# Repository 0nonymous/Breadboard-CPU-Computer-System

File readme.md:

# 8-Bit Microcoded Breadboard CPU

## Overview

This project is a fully microcoded 8-bit CPU designed from scratch and implemented using 100+ 74LS-series ICs across 40+ breadboards.

The system includes:

- Custom 8-bit CISC-style instruction set (0x00–0x45 implemented)
- 8-bit data bus
- 16-bit address bus (64KB address space)
- Fully horizontal microcoded control unit (48-bit control word)
- 6 × AT28C16 EEPROM control store
- Memory-mapped I/O
- 6522 VIA interface (32 GPIO)
- Dual-port shared memory VGA subsystem
- Custom Python two-pass assembler and ROM flashing pipeline
- Working assembly programs including Snake

This is the third architectural iteration. Earlier versions exposed architectural limitations. The current version runs reliably at approximately ~0.25 MHz.

---

## Assembly Syntax

The assembler uses suffix symbols to indicate addressing modes:

- `$` = Immediate
- `@` = Absolute
- `#` = Indirect (pointer-based)
- `&` = Absolute + X offset
- No suffix = Implied

Example:
```
lda $10
lda @2000
lda #3000
lda &4000
inx
```

---

## Complete Instruction Encoding Table

```
0x00  lda $
0x01  lda @
0x02  lda #
0x03  lda &

0x04  ldx $
0x05  ldx @
0x06  ldx #
0x07  ldx &

0x08  inx
0x09  dex
0x0A  txa
0x0B  tax

0x0C  add $
0x0D  add @
0x0E  add #
0x0F  add &

0x10  sub $
0x11  sub @
0x12  sub #
0x13  sub &

0x14  adc $
0x15  adc @
0x16  adc #
0x17  adc &

0x18  sbc $
0x19  sbc @
0x1A  sbc #
0x1B  sbc &

0x1C  and $
0x1D  and @
0x1E  and #
0x1F  and &

0x20  orr $
0x21  orr @
0x22  orr #
0x23  orr &

0x24  shr
0x25  shl
0x26  ror
0x27  rol

0x28  sta @
0x29  sta #
0x2A  sta &

0x2B  stx @
0x2C  stx #
0x2D  stx &

0x2E  pla
0x2F  pha
0x30  plx
0x31  phx
0x32  plf
0x33  phf

0x34  xla
0x35  xlx

0x36  jsr @
0x37  rsr

0x38  clf
0x39  msk
0x3A  umk

0x3B  jmp @
0x3C  beq @
0x3D  bne @
0x3E  bmi @
0x3F  bpl @
0x40  bcs @
0x41  bcc @

0x42  ila
0x43  ilx
0x44  isa
0x45  isx
```

---

## CPU Architecture

### Registers

- A — 8-bit accumulator
- B — 8-bit helper register
- X — 8-bit index register
- SP — 8-bit stack pointer (descending from 0xFF)
- PC — 16-bit program counter
- MAR — 16-bit memory address register
- IR — 8-bit instruction register
- Flags (3-bit):
  - Zero
  - Carry
  - Negative

---

## Buses and Datapath

- 8-bit internal data bus
- 16-bit address bus
- Shared bus architecture with gated register in/out signals
- MAR handles memory addressing
- PC high/low bytes independently gated

---

## ALU Implementation

The ALU is implemented using discrete TTL logic:

- 74LS283 — Addition core
- 74LS86 — 2's Complement
- 74LS08 — AND
- 74LS32 — OR
- Shift/rotate implemented via combinational wiring and arithmetic reuse
- Flag updates controlled via microcode signals (C SET, SZ SET, etc.)

---

## Microcoded Control Unit

The CPU uses a horizontal microcode architecture.

- Microinstruction width: 48 bits
- Control store: 6 × AT28C16 EEPROMs
- Microaddress width: 11 bits
- Microaddress formation:
  opcode[7:0] || microstep[2:0]
- Maximum microsteps per instruction: 7 (+ fetch cycle)

The microstep counter increments sequentially and overflows to reset.

Conditional branches do not alter microcode sequencing.  
Instead, discrete logic gates PC load signals based on flag conditions (Z, C, S).

Each microinstruction directly drives register enables, ALU operations, bus drivers, PC control, memory read/write, and flag updates.

---

## Memory Map

Total address space: 64KB

Current configuration includes:

- 2KB ROM
- 6522 VIA (32 GPIO)
- Memory-mapped I/O
- ~512B dual-port shared RAM (VGA subsystem)

Stack resides in a dedicated page and grows downward.

---

## VGA Subsystem

The CPU integrates with a separate VGA driver module.

Features:

- Text mode output
- 25 columns × 16 rows
- Hardware-assisted scrolling
- Dual-port shared memory interface between CPU and VGA driver
- Polling-based communication

The CPU writes character data into shared dual-port memory.  
The VGA module independently reads this memory to generate video timing and pixel output.

VGA signal generation approach was inspired by Ben Eater’s methodology and adapted for this architecture.

---

## Toolchain

Custom Python-based programming pipeline:

Two-pass assembler:
- Pass 1: label resolution
- Pass 2: opcode and operand encoding

Outputs a hex array representation of machine code.

A secondary Python script converts the output into binary format for ROM flashing via XGPro.

---

## Programs Written

- Instruction verification programs
- Fibonacci sequence
- Calculator utilities
- Keypad-driven applications
- VGA name/text rendering
- Snake (fully playable)

---

## Hardware Engineering and Debugging

Major issue encountered:
- Race condition causing unintended PC double-increment due to propagation delay

Debugging involved:

- Oscilloscope-based timing analysis
- Star power distribution layout
- Extensive decoupling capacitors
- Signal integrity stabilization

System runs reliably at approximately ~1 MHz.  
Estimated current draw: ~1.2–1.6A under load.

---

## Design Influences

- Instruction set loosely inspired by 6502 concepts
- Breadboard methodology and VGA experimentation influenced by Ben Eater
- Control logic, ISA structure, microcode, and integration independently designed

---

## Future Work

- Implement machine code monitor
- Potential RISC-style redesign
- FPGA implementation exploration
- Pipelining experimentation

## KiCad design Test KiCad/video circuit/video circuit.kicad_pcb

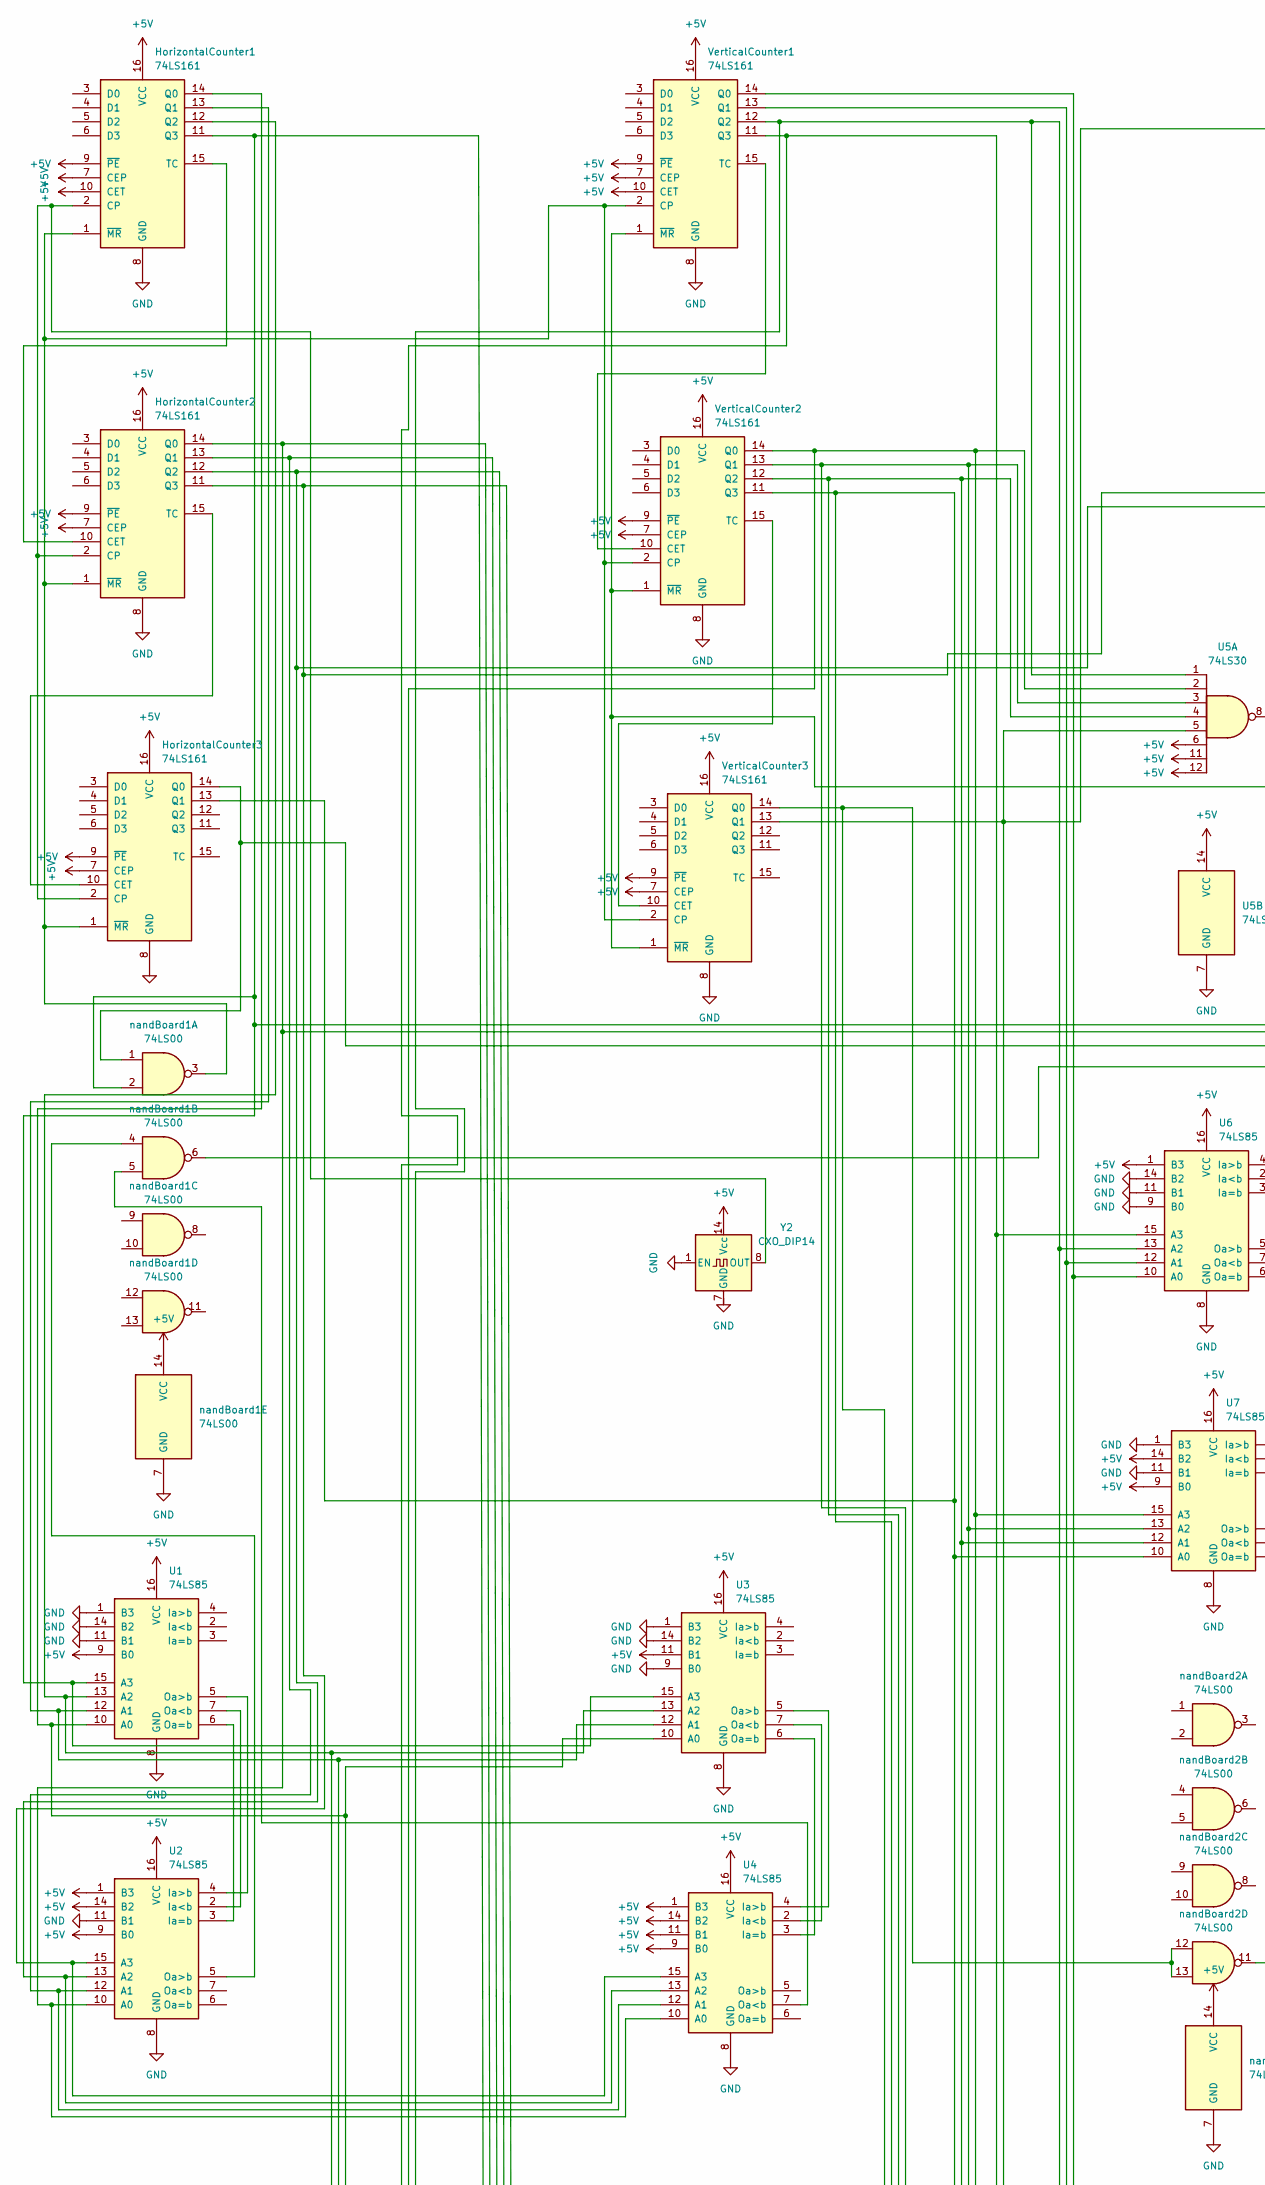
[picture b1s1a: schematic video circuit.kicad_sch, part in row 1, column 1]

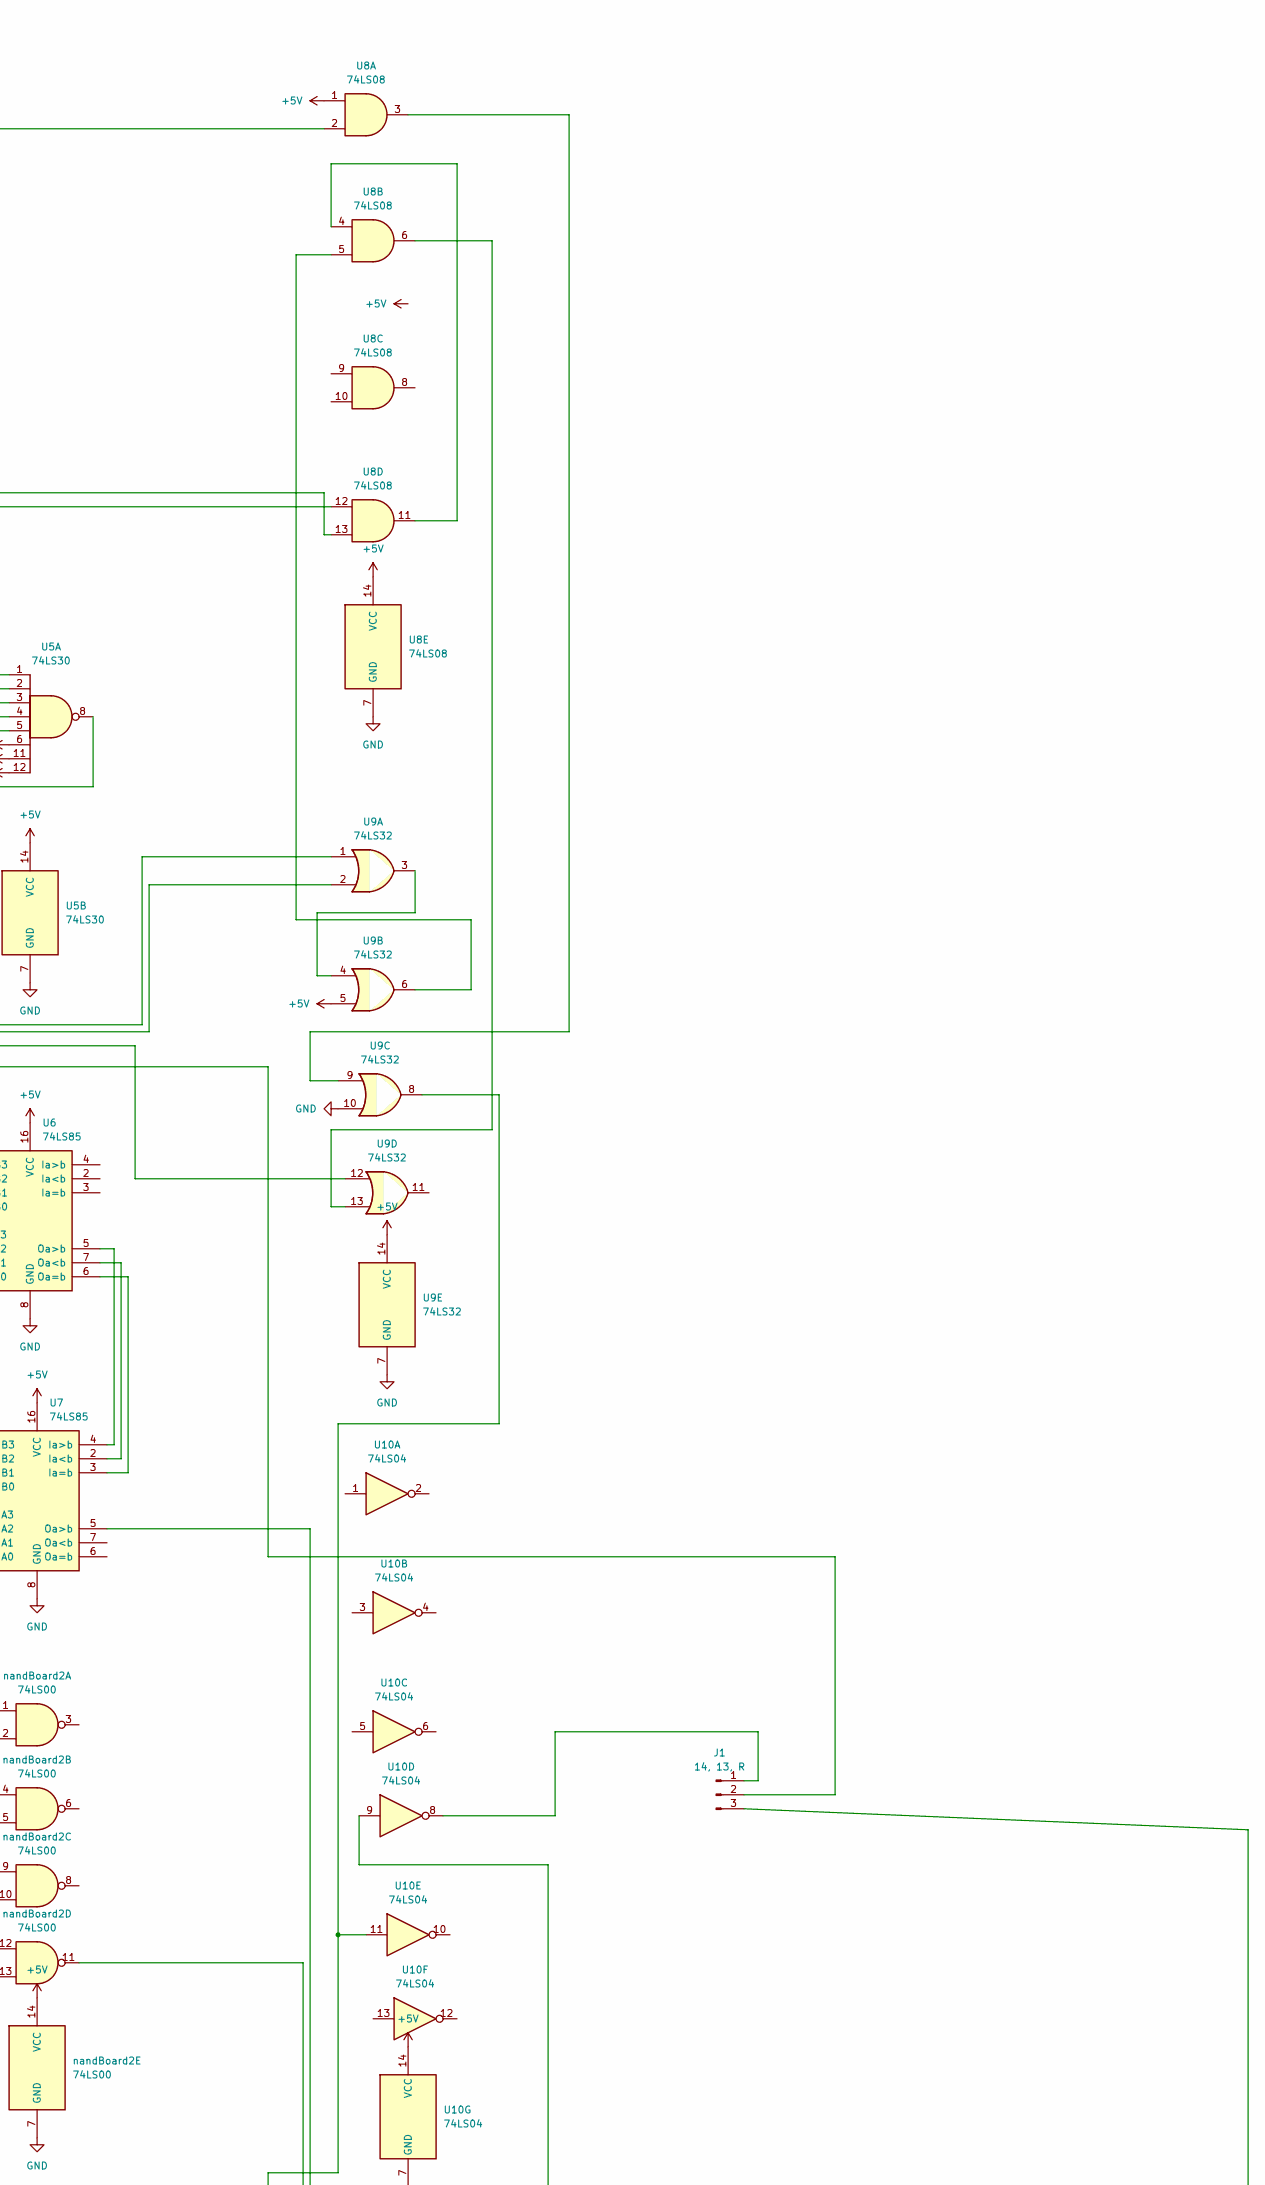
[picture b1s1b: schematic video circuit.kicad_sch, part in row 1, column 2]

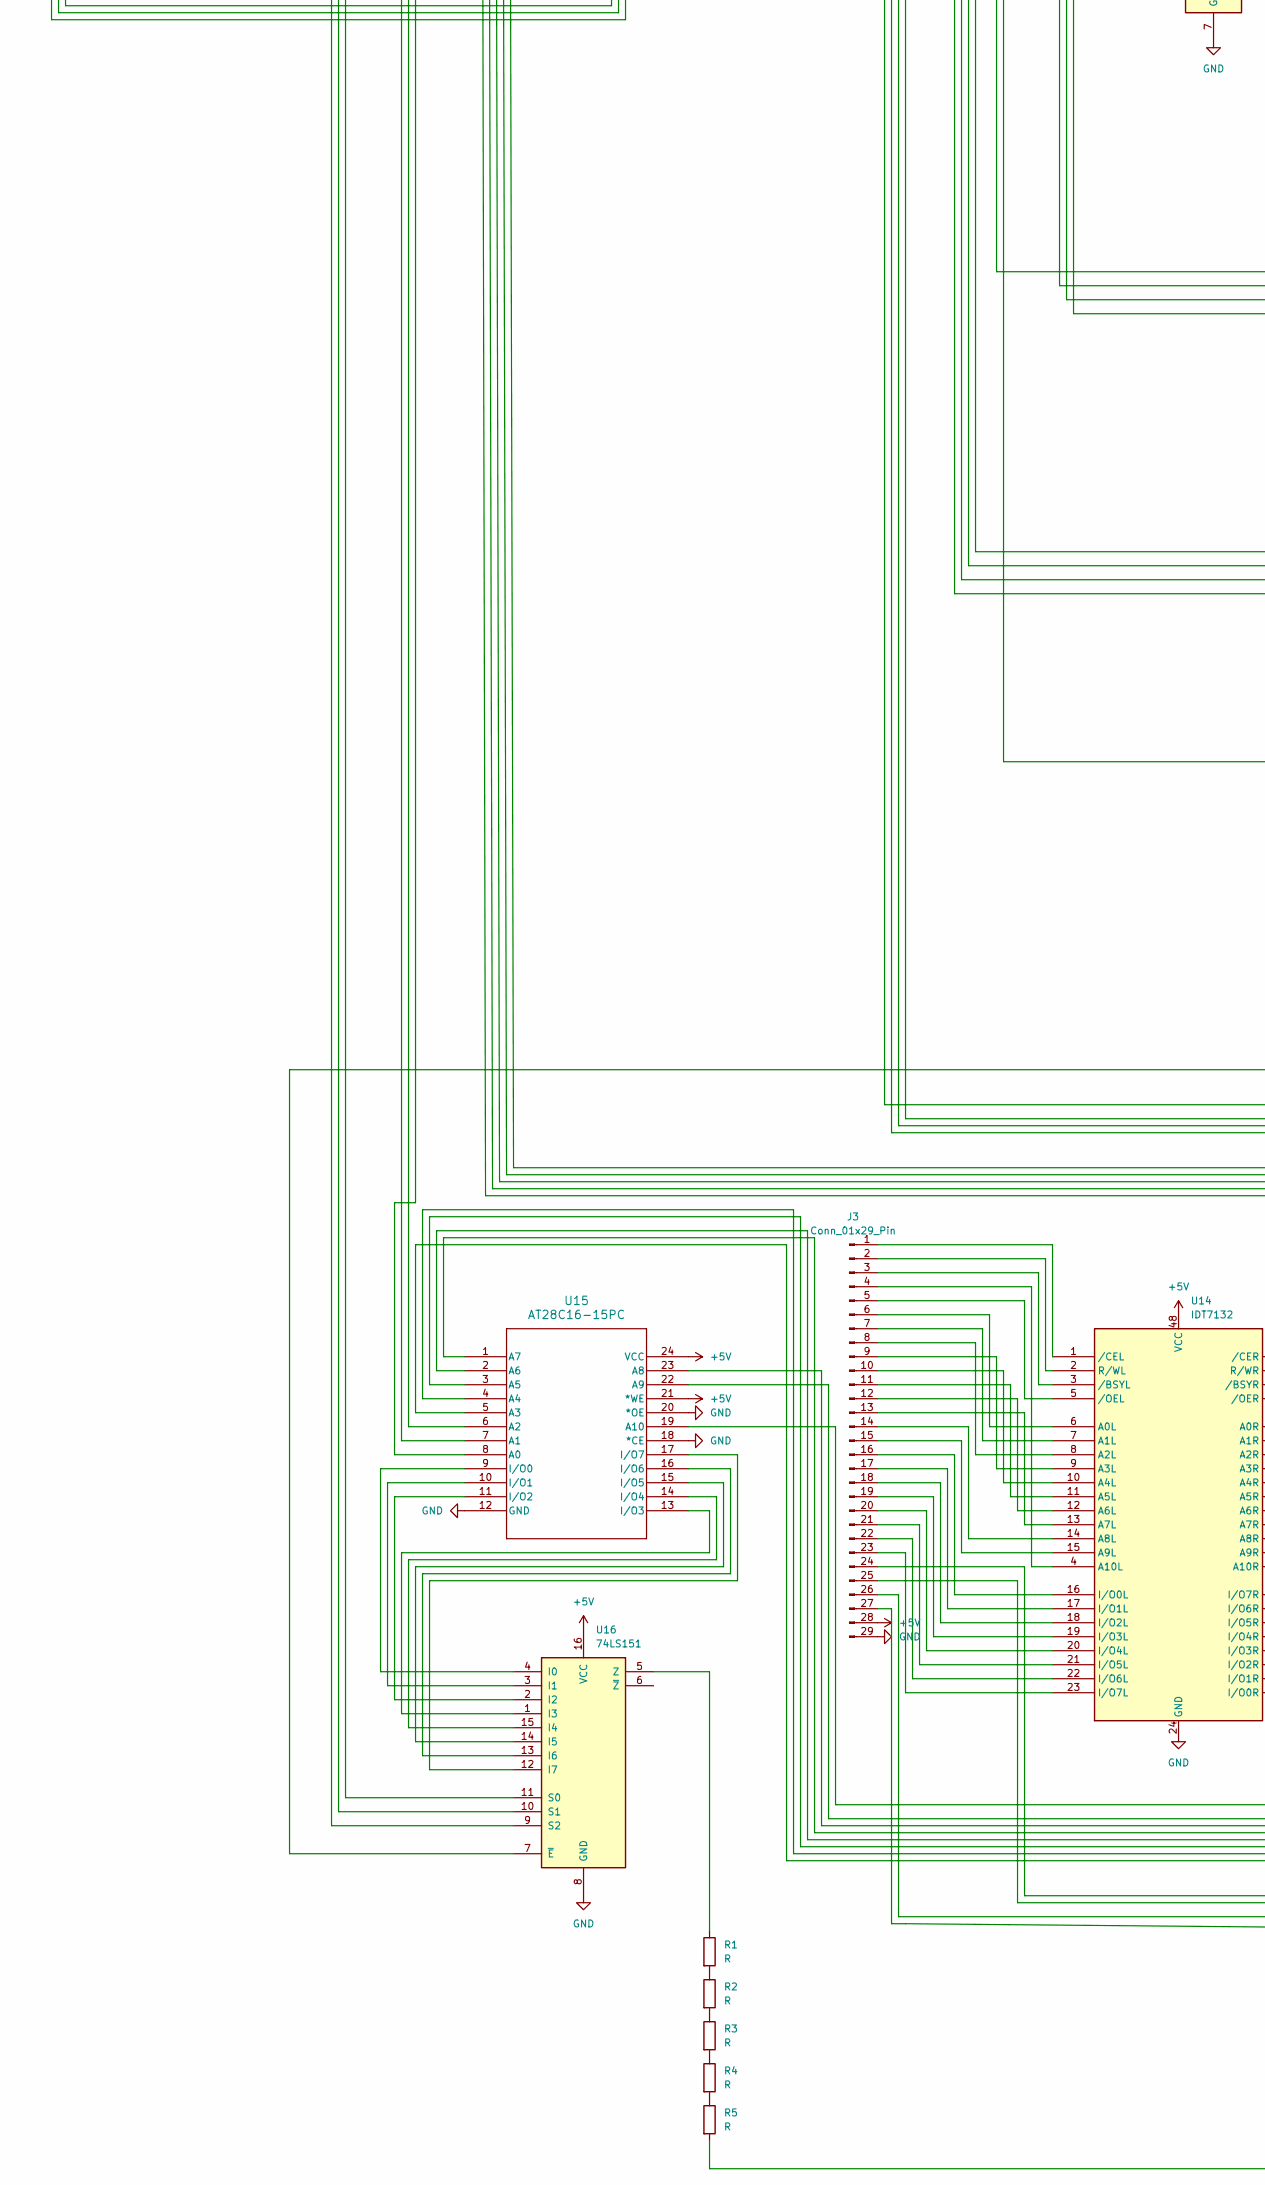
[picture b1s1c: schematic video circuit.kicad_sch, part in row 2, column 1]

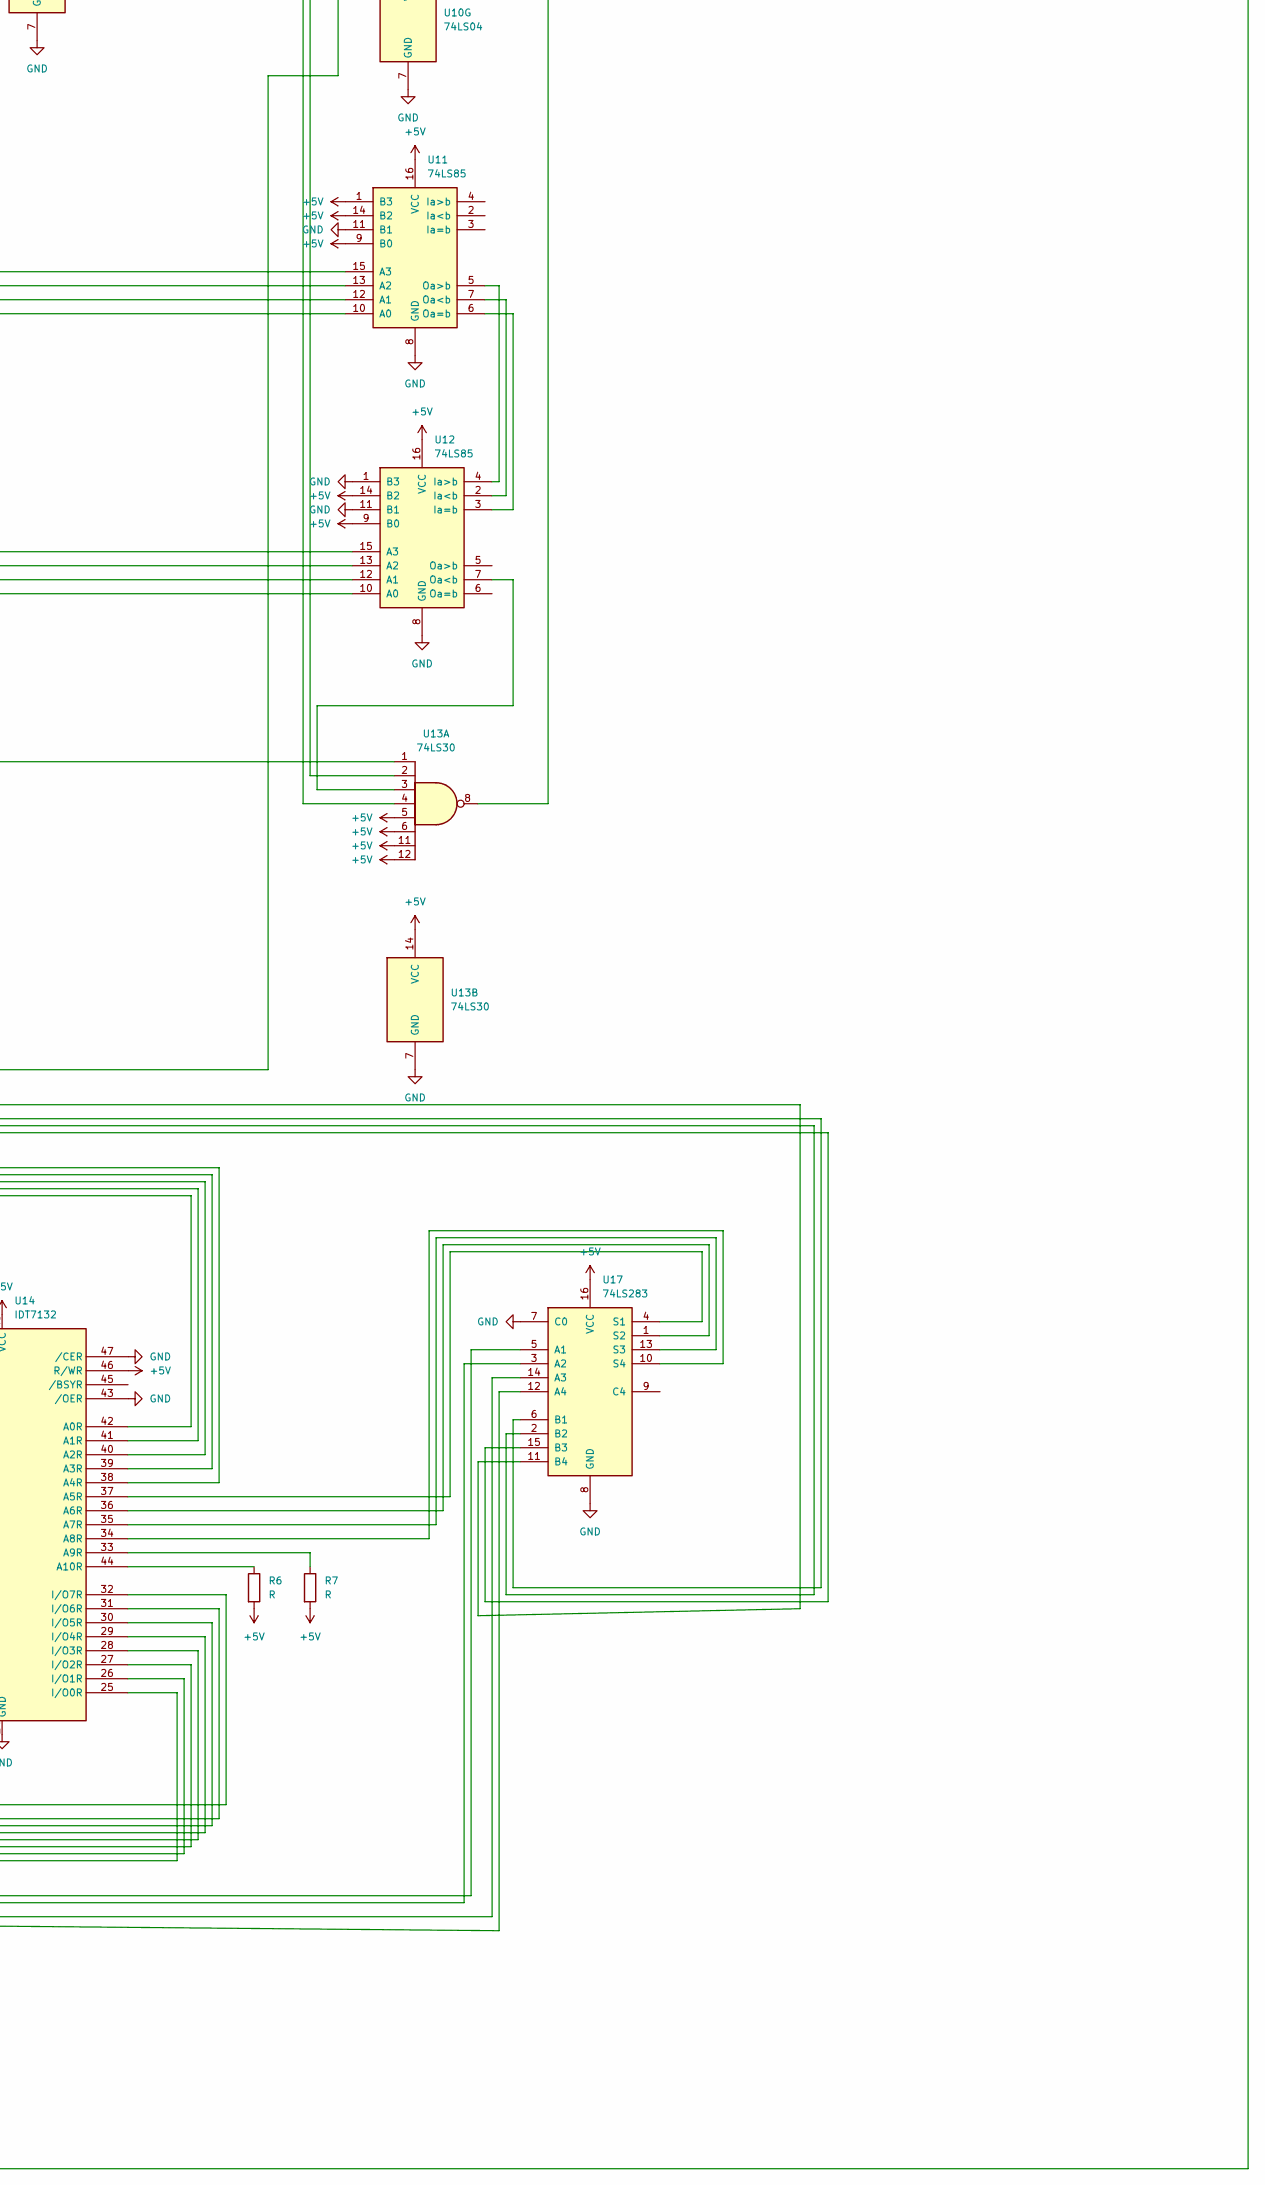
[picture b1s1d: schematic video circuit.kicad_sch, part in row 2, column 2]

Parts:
HorizontalCounter1, HorizontalCounter2, HorizontalCounter3: 74LS161; DIP-16_W7.62mm_Socket_LongPads
J1: 14, 13, R; PinHeader_1x03_P2.54mm_Vertical
J3: Conn_01x29_Pin; PinHeader_1x29_P2.54mm_Vertical
R1, R2, R3, R4, R5, R6, R7: R; R_Axial_DIN0204_L3.6mm_D1.6mm_P5.08mm_Horizontal
U1, U2, U3, U4, U6, U7, U11, U12: 74LS85; DIP-16_W7.62mm_Socket_LongPads
U5, U13: 74LS30; DIP-14_W7.62mm_Socket_LongPads
U8: 74LS08; DIP-14_W7.62mm_Socket_LongPads
U9: 74LS32; DIP-14_W7.62mm_Socket_LongPads
U10: 74LS04; DIP-14_W7.62mm_Socket_LongPads
U14: IDT7132; DIP-48_W15.24mm_LongPads
U15: AT28C16-15PC; PDIP24_14P4X32P3_MCH
U16: 74LS151; DIP-16_W7.62mm_LongPads
U17: 74LS283; DIP-16_W7.62mm_LongPads
VerticalCounter1, VerticalCounter2, VerticalCounter3: 74LS161; DIP-16_W7.62mm_Socket_LongPads
Y2: CXO_DIP14; Oscillator_DIP-14
nandBoard1, nandBoard2: 74LS00; DIP-14_W7.62mm_Socket_LongPads

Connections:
+5V: HorizontalCounter1.7 (CEP), HorizontalCounter1.9 (~PE), HorizontalCounter1.10 (CET), HorizontalCounter1.16 (VCC), HorizontalCounter2.7 (CEP), HorizontalCounter2.9 (~PE), HorizontalCounter2.16 (VCC), HorizontalCounter3.7 (CEP), HorizontalCounter3.9 (~PE), HorizontalCounter3.16 (VCC), J3.28, R6.2, R7.2, U1.9 (B0), U1.16 (VCC), U2.1 (B3), U2.9 (B0), U2.14 (B2), U2.16 (VCC), U3.11 (B1), U3.16 (VCC), U4.1 (B3), U4.9 (B0), U4.11 (B1), U4.14 (B2), U4.16 (VCC), U5.6, U5.11, U5.12, U5.14 (VCC), U6.1 (B3), U6.16 (VCC), U7.9 (B0), U7.14 (B2), U7.16 (VCC), U8.1, U8.14 (VCC), U9.5, U9.14 (VCC), U10.14 (VCC), U11.1 (B3), U11.9 (B0), U11.14 (B2), U11.16 (VCC), U12.9 (B0), U12.14 (B2), U12.16 (VCC), U13.5, U13.6, U13.11, U13.12, U13.14 (VCC), U14.46 (R/WR), U14.48 (VCC), U15.21 (*WE), U15.24 (VCC), U16.16 (VCC), U17.16 (VCC), VerticalCounter1.7 (CEP), VerticalCounter1.9 (~PE), VerticalCounter1.10 (CET), VerticalCounter1.16 (VCC), VerticalCounter2.7 (CEP), VerticalCounter2.9 (~PE), VerticalCounter2.16 (VCC), VerticalCounter3.7 (CEP), VerticalCounter3.9 (~PE), VerticalCounter3.16 (VCC), Y2.14 (Vcc), nandBoard1.14 (VCC), nandBoard2.14 (VCC)
GND: HorizontalCounter1.8 (GND), HorizontalCounter2.8 (GND), HorizontalCounter3.8 (GND), J3.29, U1.1 (B3), U1.8 (GND), U1.11 (B1), U1.14 (B2), U2.8 (GND), U2.11 (B1), U3.1 (B3), U3.8 (GND), U3.9 (B0), U3.14 (B2), U4.8 (GND), U5.7 (GND), U6.8 (GND), U6.9 (B0), U6.11 (B1), U6.14 (B2), U7.1 (B3), U7.8 (GND), U7.11 (B1), U8.7 (GND), U9.7 (GND), U9.10, U10.7 (GND), U11.8 (GND), U11.11 (B1), U12.1 (B3), U12.8 (GND), U12.11 (B1), U13.7 (GND), U14.24 (GND), U14.43 (/OER), U14.47 (/CER), U15.12 (GND), U15.18 (*CE), U15.20 (*OE), U16.8 (GND), U17.7 (C0), U17.8 (GND), VerticalCounter1.8 (GND), VerticalCounter2.8 (GND), VerticalCounter3.8 (GND), Y2.1 (EN), nandBoard1.7 (GND), nandBoard2.7 (GND)
unnamed: HorizontalCounter1.2 (CP), HorizontalCounter2.2 (CP), HorizontalCounter3.2 (CP), Y2.8 (OUT)
unnamed: HorizontalCounter1.14 (Q0), U1.10 (A0), U3.10 (A0), U16.11 (S0)
unnamed: HorizontalCounter1.13 (Q1), U1.12 (A1), U3.12 (A1), U16.10 (S1)
unnamed: HorizontalCounter1.12 (Q2), U1.13 (A2), U3.13 (A2), U16.9 (S2)
unnamed: HorizontalCounter1.11 (Q3), U1.15 (A3), U3.15 (A3), U9.1, U14.42 (A0R), nandBoard1.2
unnamed: HorizontalCounter1.15 (TC), HorizontalCounter2.10 (CET)
unnamed: HorizontalCounter1.1 (~MR), HorizontalCounter2.1 (~MR), HorizontalCounter3.1 (~MR), VerticalCounter1.2 (CP), VerticalCounter2.2 (CP), VerticalCounter3.2 (CP), nandBoard1.3
unnamed: HorizontalCounter2.14 (Q0), U2.10 (A0), U4.10 (A0), U9.2, U14.41 (A1R)
unnamed: HorizontalCounter2.13 (Q1), U2.12 (A1), U4.12 (A1), U14.40 (A2R)
unnamed: HorizontalCounter2.12 (Q2), U2.13 (A2), U4.13 (A2), U8.12, U14.39 (A3R)
unnamed: HorizontalCounter2.11 (Q3), U2.15 (A3), U4.15 (A3), U8.13, U14.38 (A4R)
unnamed: HorizontalCounter2.15 (TC), HorizontalCounter3.10 (CET)
unnamed: HorizontalCounter3.14 (Q0), U9.12, nandBoard1.1
unnamed: HorizontalCounter3.13 (Q1), U7.10 (A0), U12.10 (A0), U17.15 (B3), VerticalCounter2.11 (Q3)
unnamed: J1.1, U10.8
unnamed: J1.2, nandBoard1.6
unnamed: J1.3, R5.2
unnamed: J3.1, U14.1 (/CEL)
unnamed: J3.2, U14.2 (R/WL)
unnamed: J3.3, U14.3 (/BSYL)
unnamed: J3.4, U14.4 (A10L)
unnamed: J3.5, U14.5 (/OEL)
unnamed: J3.6, U14.6 (A0L)
unnamed: J3.7, U14.7 (A1L)
unnamed: J3.8, U14.8 (A2L)
unnamed: J3.9, U14.9 (A3L)
unnamed: J3.10, U14.10 (A4L)
unnamed: J3.11, U14.11 (A5L)
unnamed: J3.12, U14.12 (A6L)
unnamed: J3.13, U14.13 (A7L)
unnamed: J3.14, U14.14 (A8L)
unnamed: J3.15, U14.15 (A9L)
unnamed: J3.16, U14.16 (I/O0L)
unnamed: J3.17, U14.17 (I/O1L)
unnamed: J3.18, U14.18 (I/O2L)
unnamed: J3.19, U14.19 (I/O3L)
unnamed: J3.20, U14.20 (I/O4L)
unnamed: J3.21, U14.21 (I/O5L)
unnamed: J3.22, U14.22 (I/O6L)
unnamed: J3.23, U14.23 (I/O7L)
unnamed: J3.24, U17.5 (A1)
unnamed: J3.25, U17.3 (A2)
unnamed: J3.26, U17.14 (A3)
unnamed: J3.27, U17.12 (A4)
unnamed: R1.2, R2.1
unnamed: R2.2, R3.1
unnamed: R3.2, R4.1
unnamed: R4.2, R5.1
unnamed: U1.7 (Oa<b), U2.2 (Ia<b)
unnamed: U1.6 (Oa=b), U2.3 (Ia=b)
unnamed: U1.5 (Oa>b), U2.4 (Ia>b)
unnamed: U2.5 (Oa>b), nandBoard1.4
unnamed: U3.7 (Oa<b), U4.2 (Ia<b)
unnamed: U3.6 (Oa=b), U4.3 (Ia=b)
unnamed: U3.5 (Oa>b), U4.4 (Ia>b)
unnamed: U4.7 (Oa<b), nandBoard1.5
unnamed: U6.7 (Oa<b), U7.2 (Ia<b)
unnamed: U6.6 (Oa=b), U7.3 (Ia=b)
unnamed: U6.5 (Oa>b), U7.4 (Ia>b)
unnamed: U7.5 (Oa>b), U13.2
unnamed: U8.3, U9.9
unnamed: U8.5, U9.6
unnamed: U8.6, U9.13
unnamed: U8.4, U8.11
unnamed: U9.3, U9.4
unnamed: U10.9, U13.8
unnamed: U6.10 (A0), U11.10 (A0), VerticalCounter1.14 (Q0)
unnamed: U6.12 (A1), U11.12 (A1), VerticalCounter1.13 (Q1)
unnamed: U5.1, U6.13 (A2), U11.13 (A2), U15.8 (A0), VerticalCounter1.12 (Q2)
unnamed: U6.15 (A3), U11.15 (A3), U15.7 (A1), VerticalCounter1.11 (Q3)
unnamed: U11.7 (Oa<b), U12.2 (Ia<b)
unnamed: U11.6 (Oa=b), U12.3 (Ia=b)
unnamed: U11.5 (Oa>b), U12.4 (Ia>b)
unnamed: U5.4, U7.12 (A1), U12.12 (A1), U17.2 (B2), VerticalCounter2.12 (Q2)
unnamed: U5.3, U7.13 (A2), U12.13 (A2), U17.6 (B1), VerticalCounter2.13 (Q1)
unnamed: U5.2, U7.15 (A3), U12.15 (A3), U15.6 (A2), VerticalCounter2.14 (Q0)
unnamed: U12.7 (Oa<b), U13.3
unnamed: U13.4, nandBoard2.11
unnamed: U14.37 (A5R), U17.4 (S1)
unnamed: U14.36 (A6R), U17.1 (S2)
unnamed: U14.35 (A7R), U17.13 (S3)
unnamed: U14.34 (A8R), U17.10 (S4)
unnamed: R7.1, U14.33 (A9R)
unnamed: R6.1, U14.44 (A10R)
unnamed: U14.25 (I/O0R), U15.5 (A3)
unnamed: U14.26 (I/O1R), U15.4 (A4)
unnamed: U14.27 (I/O2R), U15.3 (A5)
unnamed: U14.28 (I/O3R), U15.2 (A6)
unnamed: U14.29 (I/O4R), U15.1 (A7)
unnamed: U14.30 (I/O5R), U15.23 (A8)
unnamed: U14.31 (I/O6R), U15.22 (A9)
unnamed: U14.32 (I/O7R), U15.19 (A10)
unnamed: U15.9 (I/O0), U16.4 (I0)
unnamed: U15.10 (I/O1), U16.3 (I1)
unnamed: U15.11 (I/O2), U16.2 (I2)
unnamed: U15.13 (I/O3), U16.1 (I3)
unnamed: U15.14 (I/O4), U16.15 (I4)
unnamed: U15.15 (I/O5), U16.14 (I5)
unnamed: U15.16 (I/O6), U16.13 (I6)
unnamed: U15.17 (I/O7), U16.12 (I7)
unnamed: R1.1, U16.5 (Z)
unnamed: U9.8, U10.11, U16.7 (~E)
unnamed: U17.11 (B4), VerticalCounter3.14 (Q0), nandBoard2.12, nandBoard2.13
unnamed: VerticalCounter1.15 (TC), VerticalCounter2.10 (CET)
unnamed: U5.8, VerticalCounter1.1 (~MR), VerticalCounter2.1 (~MR), VerticalCounter3.1 (~MR)
unnamed: VerticalCounter2.15 (TC), VerticalCounter3.10 (CET)
unnamed: U5.5, U8.2, U13.1, VerticalCounter3.13 (Q1)

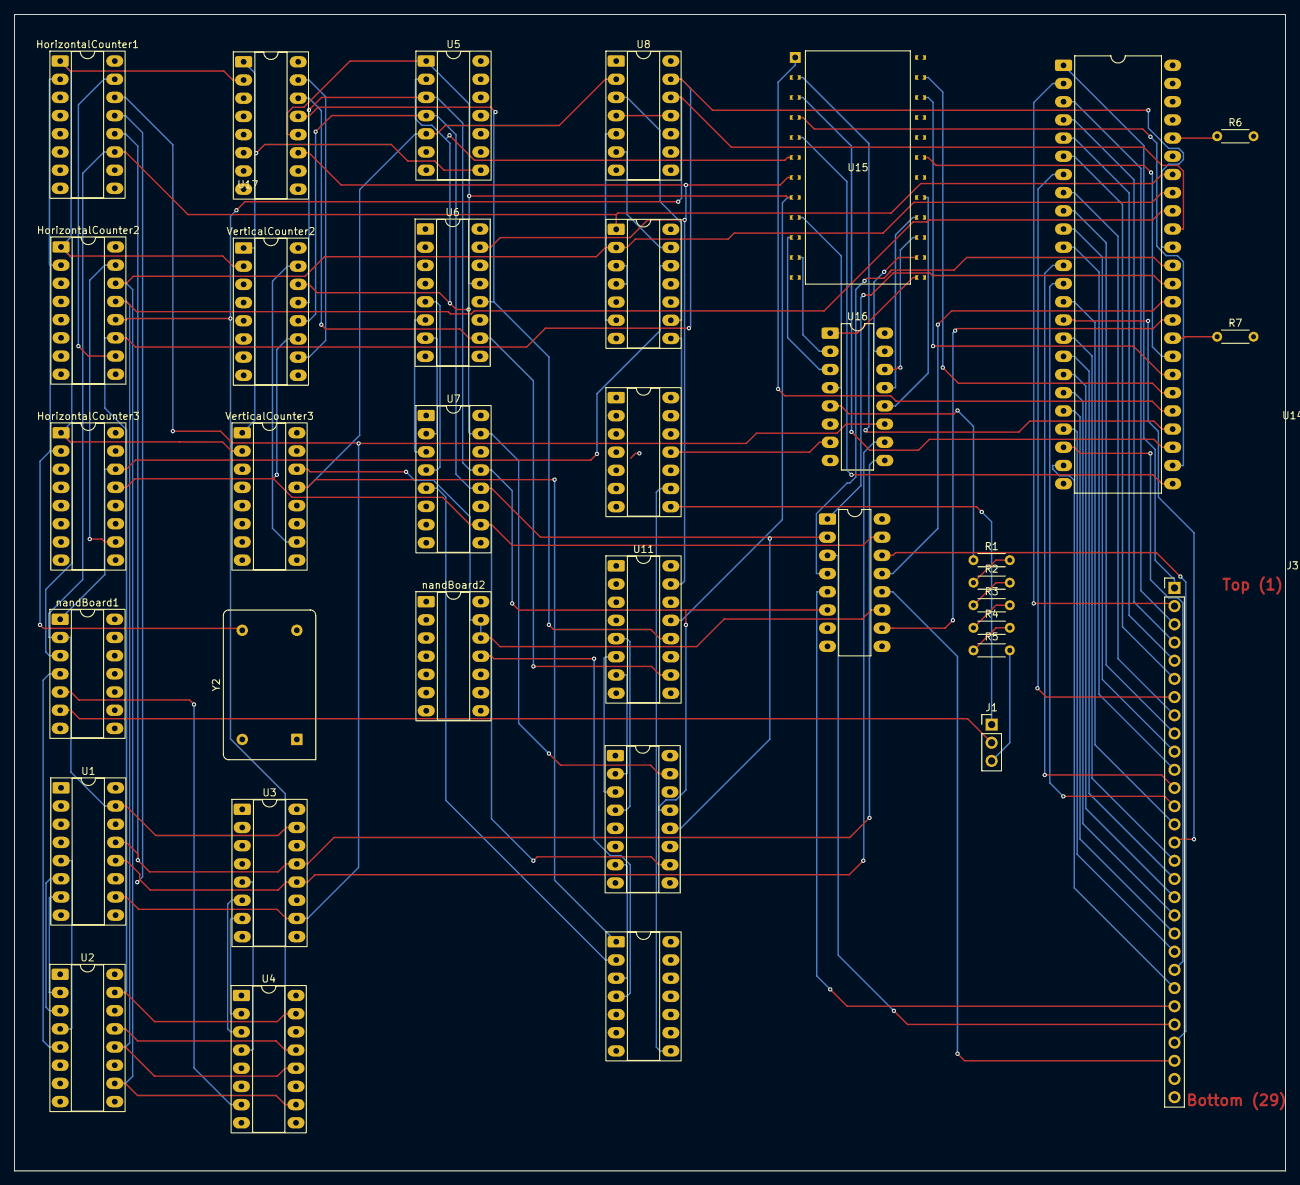
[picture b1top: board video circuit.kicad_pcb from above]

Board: 2 copper layers, 177.5 x 161.5 mm, 35 parts (0 on the bottom side), 109 nets.

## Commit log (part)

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2024-07-25 7/25/2024
2026-02-17 test
